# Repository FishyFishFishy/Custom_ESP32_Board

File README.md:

# Custom_ESP32_Board
Making a custom ESP32 Board for generic use

After making my devboard with an RP2040, I wanted to have something with an ESP32 MCU. I want to use this for general purpose projects that need additional wifi/bluetooth support. In particular, I want to make some automated window blinds and a one handed soldering tool, so I am using this as a stepping stone to learn this pcb design.

This board has a USB Type-C port to flash and power it.

Schematic:

PCB Layout:

3D Model:

BOM:
| Item Description | Supplier | Supplier Part # | Mfr Part # | Qty | Unit Price | Extended Price |
| :--- | :--- | :--- | :--- | :--- | :--- | :--- |
| CAP CER 10UF 25V X5R 0805 | DigiKey | 1276-6454-1-ND | CL21A106KAYNNNG | 35 | $0.08900 | $3.12 |
| CAP CER 1UF 16V X5R 0603 | DigiKey | 1276-1034-1-ND | CL10A105KO8NNNC | 10 | $0.03100 | $0.31 |
| RES 10K OHM 1% 1/8W 0603 | DigiKey | RNCP0603FTD10K0CT-ND | RNCP0603FTD10K0 | 40 | $0.01080 | $0.43 |
| CAP CER 0.1UF 50V X7R 0603 | DigiKey | 1276-CL10B104KB8NNNLCT-ND | CL10B104KB8NNNL | 50 | $0.01800 | $0.90 |
| IC REG LINEAR 3.3V 1A SOT-223-3L | DigiKey | 4518-AMS1117-3.3CT-ND | AMS1117-3.3 | 10 | $0.20000 | $2.00 |
| CAP CER 22PF 50V C0G/NP0 0603 | DigiKey | 399-C0603C220J5GACTUCT-ND | C0603C220J5GACTU | 10 | $0.06900 | $0.69 |
| SWITCH TACTILE SPST-NO 0.05A 16V | DigiKey | CKN10504CT-ND | PTS810SJG250SMTR LFS | 20 | $0.50700 | $10.14 |
| LED BLUE CLEAR CHIP SMD | DigiKey | 160-1646-1-ND | LTST-C190TBKT | 10 | $0.09400 | $0.94 |
| RF TXRX MOD BT WIFIU.FL SMD | DigiKey | 1965-ESP32-S3-WROOM-1U-N16R8CT-ND | ESP32-S3-WROOM-1U-N16R8 | 5 | $6.56000 | $32.80 |
| RF TXRX MOD BT WIFI PCB TH SMD | DigiKey | 5407-ESP32-C3-MINI-1-H4CT-ND | ESP32-C3-MINI-1-H4 | 5 | $3.28000 | $16.40 |
| 1N5819HW-7-F (Diode 40V 1A SOD-123) | LCSC | C82544 | 1N5819HW-7-F | 20 | $0.0295 | $0.59 |
| SK6812 LED Addressable SMD-4P | LCSC | C5378720 | SK6812 | 10 | $0.0870 | $0.87 |
| 5.1kΩ ±0.1% 125mW 0805 Ceramic Resistor | LCSC | C2912598 | HoAR0805-1/8W-5.1KR-0.1% | 20 | $0.0776 | $1.55 |
| 200Ω ±0.1% 130mW 0805 Thin Film Resistor| LCSC | C2849095 | PTFR0805B200RP9 | 10 | $0.0733 | $0.73 |
| USB-C Receptacle 16-Pin Right Angle | LCSC | C2765186 | TYPE-C 16PIN 2MD(073) | 20 | $0.0615 | $1.23 |
| ESD5B5.0ST1G ESD Protection | LCSC | C93623 | ESD5B5.0ST1G | 40 | $0.0362 | $1.45 |

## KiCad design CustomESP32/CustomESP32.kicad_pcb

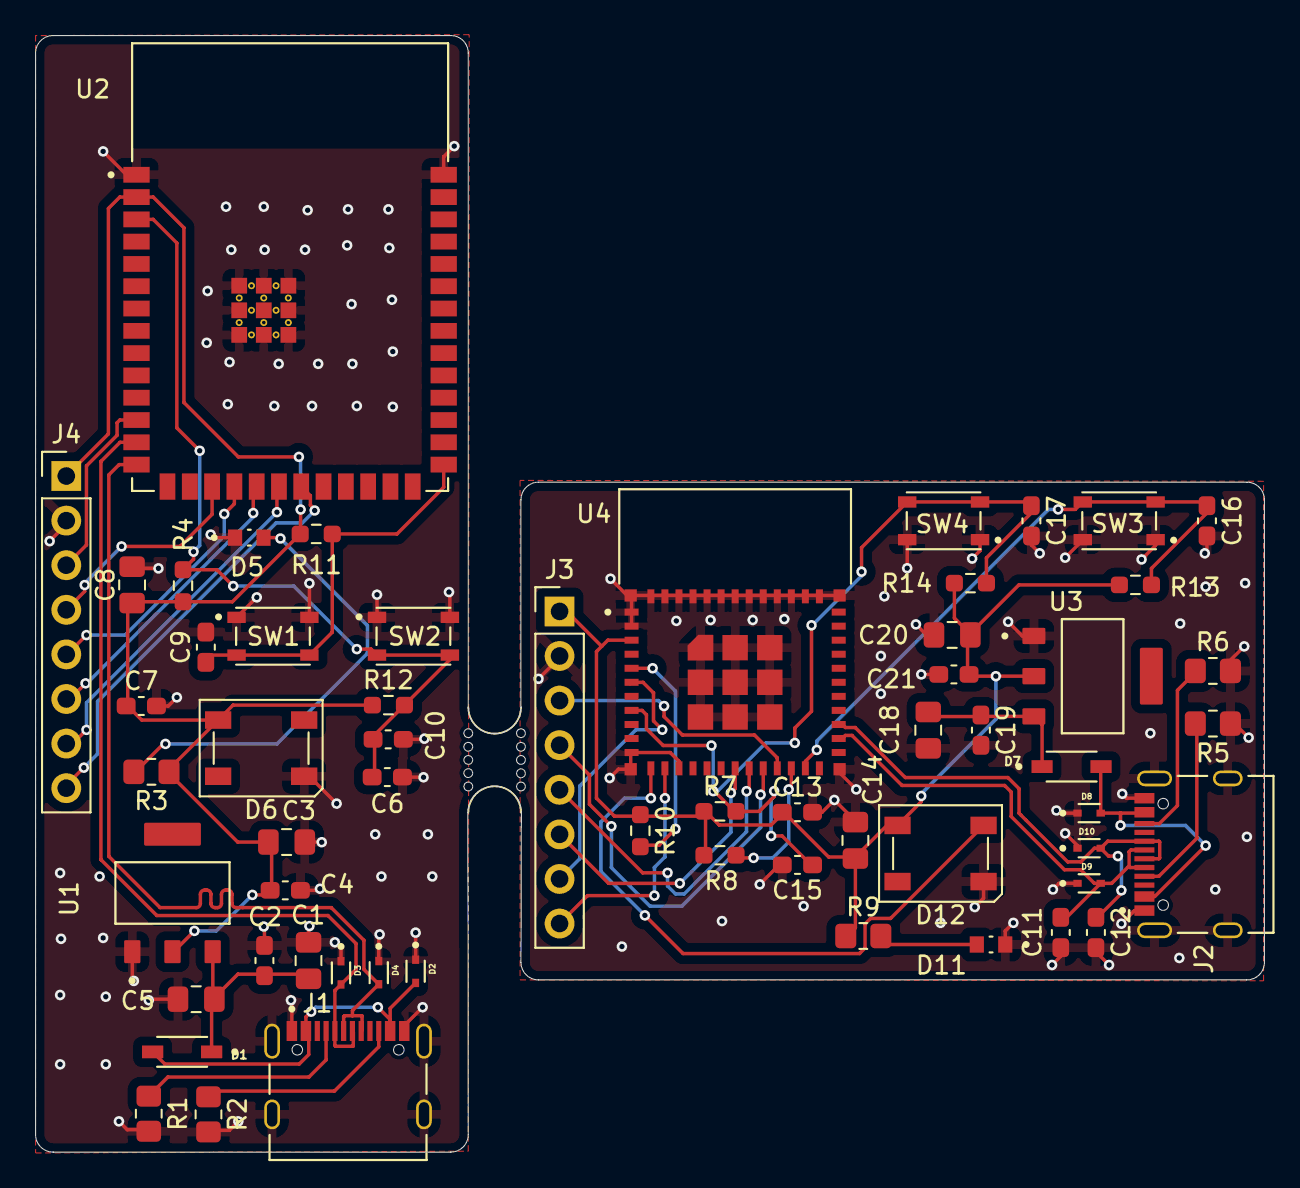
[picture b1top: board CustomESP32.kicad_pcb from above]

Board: 2 copper layers, 70.0 x 63.6 mm, 60 parts (0 on the bottom side), 35 nets.

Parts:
C1, C3, C5, C8, C14, C18, C20: 10uF; C_0805_2012Metric_Pad1.18x1.45mm_HandSolder
C2, C4, C7, C9, C10, C13, C16, C17, C19, C21: 0u1F; C_0603_1608Metric_Pad1.08x0.95mm_HandSolder
C6, C15: 1uF; C_0603_1608Metric_Pad1.08x0.95mm_HandSolder
C11, C12: 22pF; C_0603_1608Metric_Pad1.08x0.95mm_HandSolder
D1, D7: 1N5819HW-7-F; SOD3715X145N
D2, D3, D4, D8, D9, D10: LESD5D5.0CT1G; TVS_LESD5D5.0CT1G
D5, D11: LTST-C190KGKT; LEDC1608X35N
D6, D12: SK6812; LED_SK6812_PLCC4_5.0x5.0mm_P3.2mm
J1, J2: TYPE-C-31-M-12; HRO_TYPE-C-31-M-12
J3: TFTLCDC3; PinHeader_1x08_P2.54mm_Vertical
J4: TFTLCDS3; PinHeader_1x08_P2.54mm_Vertical
R1, R2, R5, R6: 5k1; R_0805_2012Metric_Pad1.20x1.40mm_HandSolder
R3, R9: 75; R_0805_2012Metric_Pad1.20x1.40mm_HandSolder
R4, R7, R8, R10, R11, R12, R13, R14: 10k; R_0603_1608Metric_Pad0.98x0.95mm_HandSolder
SW1, SW2, SW3, SW4: PTS810_SJM_250_SMTR_LFS; SW_PTS810_SJM_250_SMTR_LFS
U1, U3: AMS1117-3.3; SOT229P700X180-4N
U2: ESP32-S3-WROOM-1-N16R2; XCVR_ESP32-S3-WROOM-1-N16R2
U4: ESP32-C3-MINI-1-N4; XCVR_ESP32-C3-MINI-1-N4
mouse-bite-3mm-slot: VAL**; mouse-bite-3mm-slot

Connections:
BL: J4.8, U2.21 (IO13)
BL(2): J3.8, U4.13 (IO1)
CHIP_PU: C6.1, C10.1, R4.2, R12.2, SW2.3, SW2.4, U2.3 (EN)
CHIP_PU(2): C15.1, C17.1, R7.2, R14.2, SW4.3, SW4.4, U4.8 (EN)
CLK: J4.4, U2.17 (IO9)
CLK(2): J3.4, U4.20 (IO6)
CS: J4.5, U2.18 (IO10)
CS(2): J3.5, U4.19 (IO5)
D2+: C12.1, D10.2, J2.A6 (DP1), J2.B6 (DP2), U4.27 (IO19)
D2-: C11.1, D9.2, J2.A7 (DN1), J2.B7 (DN2), U4.26 (IO18)
D+: D4.2, J1.A6 (DP1), J1.B6 (DP2), U2.14 (IO20)
D-: D3.2, J1.A7 (DN1), J1.B7 (DN2), U2.13 (IO19)
DC: J4.6, U2.19 (IO11)
DC(2): J3.6, U4.18 (IO4)
DIN: J4.3, U2.12 (IO8)
DIN(2): J3.3, U4.21 (IO7)
ESP_3V3: C3.1, C4.1, C7.1, C8.1, D6.3 (VDD), J4.1, R3.1, R4.1, R11.1, R12.1, U1.2 (VOUT), U2.2 (3V3)
ESP_3V3(2): C13.1, C14.1, C20.1, C21.1, D12.3 (VDD), J3.1, R7.1, R8.1, R9.1, R10.1, R13.1, R14.1, U3.2 (VOUT), U4.3 (3V3)
GND: C1.2, C2.2, C3.2, C4.2, C5.2, C6.2, C7.2, C8.2, C9.2, C10.2, C11.2, C12.2, C13.2, C14.2, C15.2, C16.2, C17.2, C18.2, C19.2, C20.2, C21.2, D2.1, D3.1, D4.1, D5.C, D6.1 (VSS), D8.1, D9.1, D10.1, D11.C, D12.1 (VSS), J1.A1_B12 (GND), J1.B1_A12 (GND), J1.S1 (SHIELD), J1.S2 (SHIELD), J1.S3 (SHIELD), J1.S4 (SHIELD), J2.A1_B12 (GND), J2.B1_A12 (GND), J2.S1 (SHIELD), J2.S2 (SHIELD), J2.S3 (SHIELD), J2.S4 (SHIELD), J3.2, J4.2, R1.2, R2.2, R5.2, R6.2, SW1.1, SW1.2, SW2.1, SW2.2, SW3.1, SW3.2, SW4.1, SW4.2, U1.1 (GND/ADJ), U2.1 (GND), U2.40 (GND), U2.41_1 (GND), U2.41_2 (GND), U2.41_3 (GND), U2.41_4 (GND), U2.41_5 (GND), U2.41_6 (GND), U2.41_7 (GND), U2.41_8 (GND), U2.41_9 (GND), U3.1 (GND/ADJ), U4.1 (GND), U4.2 (GND), U4.11 (GND), U4.14 (GND), U4.36 (GND), U4.37 (GND), U4.38 (GND), U4.39 (GND), U4.40 (GND), U4.41 (GND), U4.42 (GND), U4.43 (GND), U4.44 (GND), U4.45 (GND), U4.46 (GND), U4.47 (GND), U4.48 (GND), U4.49_1 (GND), U4.49_2 (GND), U4.49_3 (GND), U4.49_4 (GND), U4.49_5 (GND), U4.49_6 (GND), U4.49_7 (GND), U4.49_8 (GND), U4.49_9 (GND), U4.50 (GND), U4.51 (GND), U4.52 (GND), U4.53 (GND)
GPIO0: C9.1, R11.2, SW1.3, SW1.4, U2.27 (IO0)
GPIO9: C16.1, R13.2, SW3.3, SW3.4, U4.23 (IO9)
unnamed: D5.A, R3.2
unnamed: D11.A, R9.2
unnamed: J1.A5 (CC1), R1.1
unnamed: J1.B5 (CC2), R2.1
unnamed: J2.A5 (CC1), R5.1
unnamed: J2.B5 (CC2), R6.1
unnamed: R10.2, U4.5 (IO2)
unnamed: R8.2, U4.22 (IO8)
RGB(2): D12.2 (DIN), U4.12 (IO0)
RST: J4.7, U2.20 (IO12)
RST(2): J3.7, U4.6 (IO3)
VBUS: D1.A, D2.2, D7.A, D8.2, J1.A4_B9 (VBUS), J1.B4_A9 (VBUS), J2.A4_B9 (VBUS), J2.B4_A9 (VBUS)
VCC_5V: C1.1, C2.1, C5.1, D1.C, U1.3 (VIN)
VCC_5V(2): C18.1, C19.1, D7.C, U3.3 (VIN)

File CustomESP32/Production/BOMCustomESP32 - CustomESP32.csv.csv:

Id,Designator,Footprint,Quantity,Designation,Supplier and ref
1,"D11,D5",LEDC1608X35N,2,LTST-C190KGKT,
2,"R14,R13,R12,R11,R10,R8,R7,R4",R_0603_1608Metric_Pad0.98x0.95mm_HandSolder,8,10k,
3,"R9,R3",R_0805_2012Metric_Pad1.20x1.40mm_HandSolder,2,75,
4,"R6,R5,R2,R1",R_0805_2012Metric_Pad1.20x1.40mm_HandSolder,4,5k1,
5,"C21,C19,C17,C16,C13,C10,C9,C7,C4,C2",C_0603_1608Metric_Pad1.08x0.95mm_HandSolder,10,0u1F,
6,"C20,C18,C14,C8,C5,C3,C1",C_0805_2012Metric_Pad1.18x1.45mm_HandSolder,7,10uF,
7,"C15,C6",C_0603_1608Metric_Pad1.08x0.95mm_HandSolder,2,1uF,
8,"C12,C11",C_0603_1608Metric_Pad1.08x0.95mm_HandSolder,2,22pF,
9,"U3,U1",SOT229P700X180-4N,2,AMS1117-3.3,
10,"D12,D6",LED_SK6812_PLCC4_5.0x5.0mm_P3.2mm,2,SK6812,
11,"D10,D8,D9,D2,D4,D3",TVS_LESD5D5.0CT1G,6,LESD5D5.0CT1G,
12,"SW3,SW4,SW2,SW1",SW_PTS810_SJM_250_SMTR_LFS,4,PTS810_SJM_250_SMTR_LFS,
13,"D7,D1",SOD3715X145N,2,1N5819HW-7-F,
14,U4,XCVR_ESP32-C3-MINI-1-N4,1,ESP32-C3-MINI-1-N4,
15,J3,PinHeader_1x08_P2.54mm_Vertical,1,TFTLCDC3,
16,"J2,J1",HRO_TYPE-C-31-M-12,2,TYPE-C-31-M-12,
17,mouse-bite-3mm-slot,mouse-bite-3mm-slot,1,VAL**,
18,J4,PinHeader_1x08_P2.54mm_Vertical,1,TFTLCDS3,
19,U2,XCVR_ESP32-S3-WROOM-1-N16R2,1,ESP32-S3-WROOM-1-N16R2,

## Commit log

2026-03-09 Enhance README with project details and images
    Added project description and images for schematic, PCB layout, and 3D model.
2026-03-09 Add BOM section to README
    Added Bill of Materials (BOM) section with component details.
2026-03-09 Update Bluetooth module quantity and pricing
2026-03-09 Update Bluetooth module description and add new item
